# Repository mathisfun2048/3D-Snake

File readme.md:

# 3-D Snake... but polished

## Description and Exigence

The basic framework of this project came from the undercity hackathon, where me and my teammates were able to scrapyard a prototype to work. This project is the same project but refined, adding a PCB to better manage wires and audio to better communicate to the user when the snake dies. Some minor software improvements have also been made (such as re-working the moving mechanism when the snake reaches the top pannel). 

Here's a pic of our prototype:

## Schematic and PCB

During prototyping, one of the hardest parts of the design was making sure all the gpio pins stayed in place! So, I made a pcb to help with wiring. 

Here's the full wirings with the raspberry pi:

## Firmware

This project is coded in circuitpython to run on a raspberry pi pico. Most of the firmware was written at the hackathon, including the snake's game engine and wrapping mechanisms. With my improvements, a audio mechanism was added, playing a sound when the game is played and a death "game over" sound. Additionally, the joystick movements was revised, however, its effacaciy will only be able to be tested once I build it and get to callibrate the joystick.

## CAD

Here it is! It's pretty bare-bones because I want access to all the gpio and other pins for debugging. 

Here's what the game will look like with the prototype cad we made at undercity! 

## BOM
|item                |quantitiy|tot. cost|FIELD4                                                                                                                                                                                                                                                                                                                                                                                                                                                                                                                                                                                     |
|--------------------|---------|---------|-------------------------------------------------------------------------------------------------------------------------------------------------------------------------------------------------------------------------------------------------------------------------------------------------------------------------------------------------------------------------------------------------------------------------------------------------------------------------------------------------------------------------------------------------------------------------------------------|
|Raspberry Pi Pico   |1        |3.94     |https://www.aliexpress.us/item/3256805901509044.html?spm=a2g0o.productlist.main.4.dbd8ce49Pw7vDJ&aem_p4p_detail=202507160215394922763879841710000065438&algo_pvid=166d0d05-e104-4c77-8e09-4d1850dd867c&algo_exp_id=166d0d05-e104-4c77-8e09-4d1850dd867c-3&pdp_ext_f={"order":"588","eval":"1"}&pdp_npi=4@dis!USD!3.94!0.99!!!28.12!7.05!@2103245417526573392084861e1d15!12000044713099471!sea!US!6423725769!ABX&curPageLogUid=9vH35S108aDJ&utparam-url=scene:search&#124;query_from:&search_p4p_id=202507160215394922763879841710000065438_1                                                    |
|8x8 Neopixel Matrix |5        |0.99     |https://www.aliexpress.us/item/3256806907950230.html?spm=a2g0o.productlist.main.1.2bbc5ce5pLgTVv&aem_p4p_detail=202507151754542105286846737200000740401&algo_pvid=230e7d87-c7e6-4e0c-8734-1b0156b671e8&algo_exp_id=230e7d87-c7e6-4e0c-8734-1b0156b671e8-0&pdp_ext_f=%7B%22order%22%3A%2225%22%2C%22eval%22%3A%221%22%7D&pdp_npi=4%40dis%21USD%212.42%210.99%21%21%2117.26%217.08%21%402103209b17526272944055213e0d20%2112000039383600775%21sea%21US%210%21ABX&curPageLogUid=1N7nF0o4iUD7&utparam-url=scene%3Asearch%7Cquery_from%3A&search_p4p_id=202507151754542105286846737200000740401_1|
|Jumper Wire Kit     |1        |2.94     |https://www.aliexpress.us/item/3256801814340687.html?spm=a2g0o.cart.0.0.18e038daN3o7c6&mp=1&pdp_npi=5@dis!USD!USD 3.11!USD 2.94!!USD 2.94!!!@2103244817526478142373005ef927!12000018371624182!ct!US!6423725769!!1!0&_gl=1*1n0i64z*_gcl_au*MTk0MzAyNDY5MC4xNzUyNjI3MjM2*_ga*MTc1NDE4NzMwOC4xNzUyNjI3MjM3*_ga_VED1YSGNC7*czE3NTI2NDcxMjIkbzMkZzEkdDE3NTI2NDc4MzAkajE2JGwwJGgw&gatewayAdapt=glo2usa                                                                                                                                                                                           |
|7 Segment Display   |2        |0.88     |https://www.aliexpress.us/item/3256806851785862.html?spm=a2g0o.productlist.main.2.76ae5146QPECX9&algo_pvid=e750615b-f244-471b-bc4a-14b7c0dba0d7&algo_exp_id=e750615b-f244-471b-bc4a-14b7c0dba0d7-1&pdp_ext_f=%7B%22order%22%3A%221740%22%2C%22eval%22%3A%221%22%2C%22orig_sl_item_id%22%3A%221005007038100614%22%2C%22orig_item_id%22%3A%221005008653444674%22%7D&pdp_npi=4%40dis%21USD%211.97%210.89%21%21%2114.02%216.31%21%402101c80217526280440434429ebc72%2112000039179020865%21sea%21US%210%21ABX&curPageLogUid=seevTTpQwIjR&utparam-url=scene%3Asearch%7Cquery_from%3A              |
|Joystick            |1        |5.54     |https://www.aliexpress.us/item/3256807375670744.html?spm=a2g0o.productlist.0.0.4dcf732baWaYuF&mp=1&pdp_npi=5%40dis%21USD%21USD%205.55%21USD%200.99%21%21USD%200.99%21%21%21%402103246617526296646986725ef22f%2112000041302774772%21ct%21US%21-1%21%211%210&_gl=1*1cuejm7*_gcl_au*Nzg2NzU0ODQ1LjE3NTI2MjcyOTg.*_ga*MTI2NzgwMDk2Ny4xNzUyNjI3NzUy*_ga_VED1YSGNC7*czE3NTI2Mjc3NTIkbzEkZzEkdDE3NTI2Mjk2NjQkajYkbDAkaDA.&gatewayAdapt=glo2usa                                                                                                                                                    |
|Stepper Motor       |1        |6.05     |https://www.aliexpress.us/item/3256802068491329.html?spm=a2g0o.productlist.main.2.5c6722b96U4iYb&algo_pvid=ff7cea5a-0fa2-4fb9-84df-aa9c87232c42&algo_exp_id=ff7cea5a-0fa2-4fb9-84df-aa9c87232c42-1&pdp_ext_f=%7B%22order%22%3A%2294%22%2C%22eval%22%3A%221%22%7D&pdp_npi=4%40dis%21USD%2117.73%210.99%21%21%2117.73%210.99%21%402101c59517526291617727360eec60%2112000030753573944%21sea%21US%210%21ABX&curPageLogUid=7Ex5kMtxOTSK&utparam-url=scene%3Asearch%7Cquery_from%3A         https://www.amazon.com/gp/product/B00PNEQKC0/ref=ewc_pr_img_3?smid=AWQBCGWISS7BL&psc=1               |
|Stepper Motor Driver|1        |2.25     |https://www.aliexpress.us/item/3256809082535036.html?spm=a2g0o.cart.0.0.4f6638da3vPkLG&mp=1&pdp_npi=5@dis!USD!USD 4.50!USD 2.25!!USD 2.25!!!@2101ead817526549979955339eefa0!12000048551339904!ct!US!6423725769!!1!0&_gl=1*1jo1tpj*_gcl_au*MTk0MzAyNDY5MC4xNzUyNjI3MjM2*_ga*MTc1NDE4NzMwOC4xNzUyNjI3MjM3*_ga_VED1YSGNC7*czE3NTI2NTMwNjIkbzQkZzEkdDE3NTI2NTQ5OTgkajU5JGwwJGgw&gatewayAdapt=glo2usa                                                                                                                                                                                           |
|9v Battery          |2        |0        |n/a                                                                                                                                                                                                                                                                                                                                                                                                                                                                                                                                                                                        |
|9V Battery Wire     |2        |1.35     |https://www.aliexpress.us/item/3256806021864359.html?spm=a2g0o.productlist.main.1.3cdc63faZErZgJ&algo_pvid=79f0a5c4-7072-47e4-94d5-bd7585c02c02&algo_exp_id=79f0a5c4-7072-47e4-94d5-bd7585c02c02-0&pdp_ext_f=%7B%22order%22%3A%22872%22%2C%22eval%22%3A%221%22%7D&pdp_npi=4%40dis%21USD%211.39%210.99%21%21%219.90%217.01%21%402103244817526291003078319ef997%2112000036283911965%21sea%21US%210%21ABX&curPageLogUid=NyxoG5DCxoBX&utparam-url=scene%3Asearch%7Cquery_from%3A                                                                                                               |
|I2C Audio Module    |1        |2.13     |https://www.aliexpress.us/item/3256807442706139.html?spm=a2g0o.cart.0.0.337d38daaIdRcX&mp=1&pdp_npi=5@dis!USD!USD 2.18!USD 2.13!!USD 2.13!!!@2103146c17526564969422213ebb51!12000041565703118!ct!US!6423725769!!1!0&_gl=1*zdge7z*_gcl_au*MTk0MzAyNDY5MC4xNzUyNjI3MjM2*_ga*MTc1NDE4NzMwOC4xNzUyNjI3MjM3*_ga_VED1YSGNC7*czE3NTI2NTMwNjIkbzQkZzEkdDE3NTI2NTY0ODMkajU4JGwwJGgw&gatewayAdapt=glo2usa                                                                                                                                                                                            |
|Speaker             |1        |1.84     |https://www.aliexpress.us/item/3256805513567413.html?spm=a2g0o.productlist.main.2.62921545em6tZ4&algo_pvid=6fd662af-376f-43c8-b7bc-04e676755f85&algo_exp_id=6fd662af-376f-43c8-b7bc-04e676755f85-1&pdp_ext_f={"order":"521","eval":"1"}&pdp_npi=4@dis!USD!1.91!0.99!!!13.62!7.02!@2103247417526569339281477efc58!12000044410928207!sea!US!6423725769!ABX&curPageLogUid=dsVUW3rp1g8F&utparam-url=scene:search&#124;query_from:                                                                                                                                                                   |
|header pins         |1        |2.21     |https://www.aliexpress.us/item/2255800687544049.html?spm=a2g0o.productlist.main.3.33dd552fLOHpHk&algo_pvid=4a50cbd5-7957-4d16-a3ac-91a9c1a7af24&algo_exp_id=4a50cbd5-7957-4d16-a3ac-91a9c1a7af24-2&pdp_ext_f={"order":"3500","eval":"1"}&pdp_npi=4@dis!USD!2.21!0.99!!!2.21!0.99!@2101e07217526574650792034e0f2b!10000010058190554!sea!US!6423725769!ABX&curPageLogUid=oeRbzI77IVV5&utparam-url=scene:search&#124;query_from:                                                                                                                                                                   |
|pcb                 |1        |6.22     |https://jlcpcb.com/                                                                                                                                                                                                                                                                                                                                                                                                                                                                                                                                                                        |
|                    |         |36.34    |                                                                                                                                                                                                                                                                                                                                                                                                                                                                                                                                                                                           |

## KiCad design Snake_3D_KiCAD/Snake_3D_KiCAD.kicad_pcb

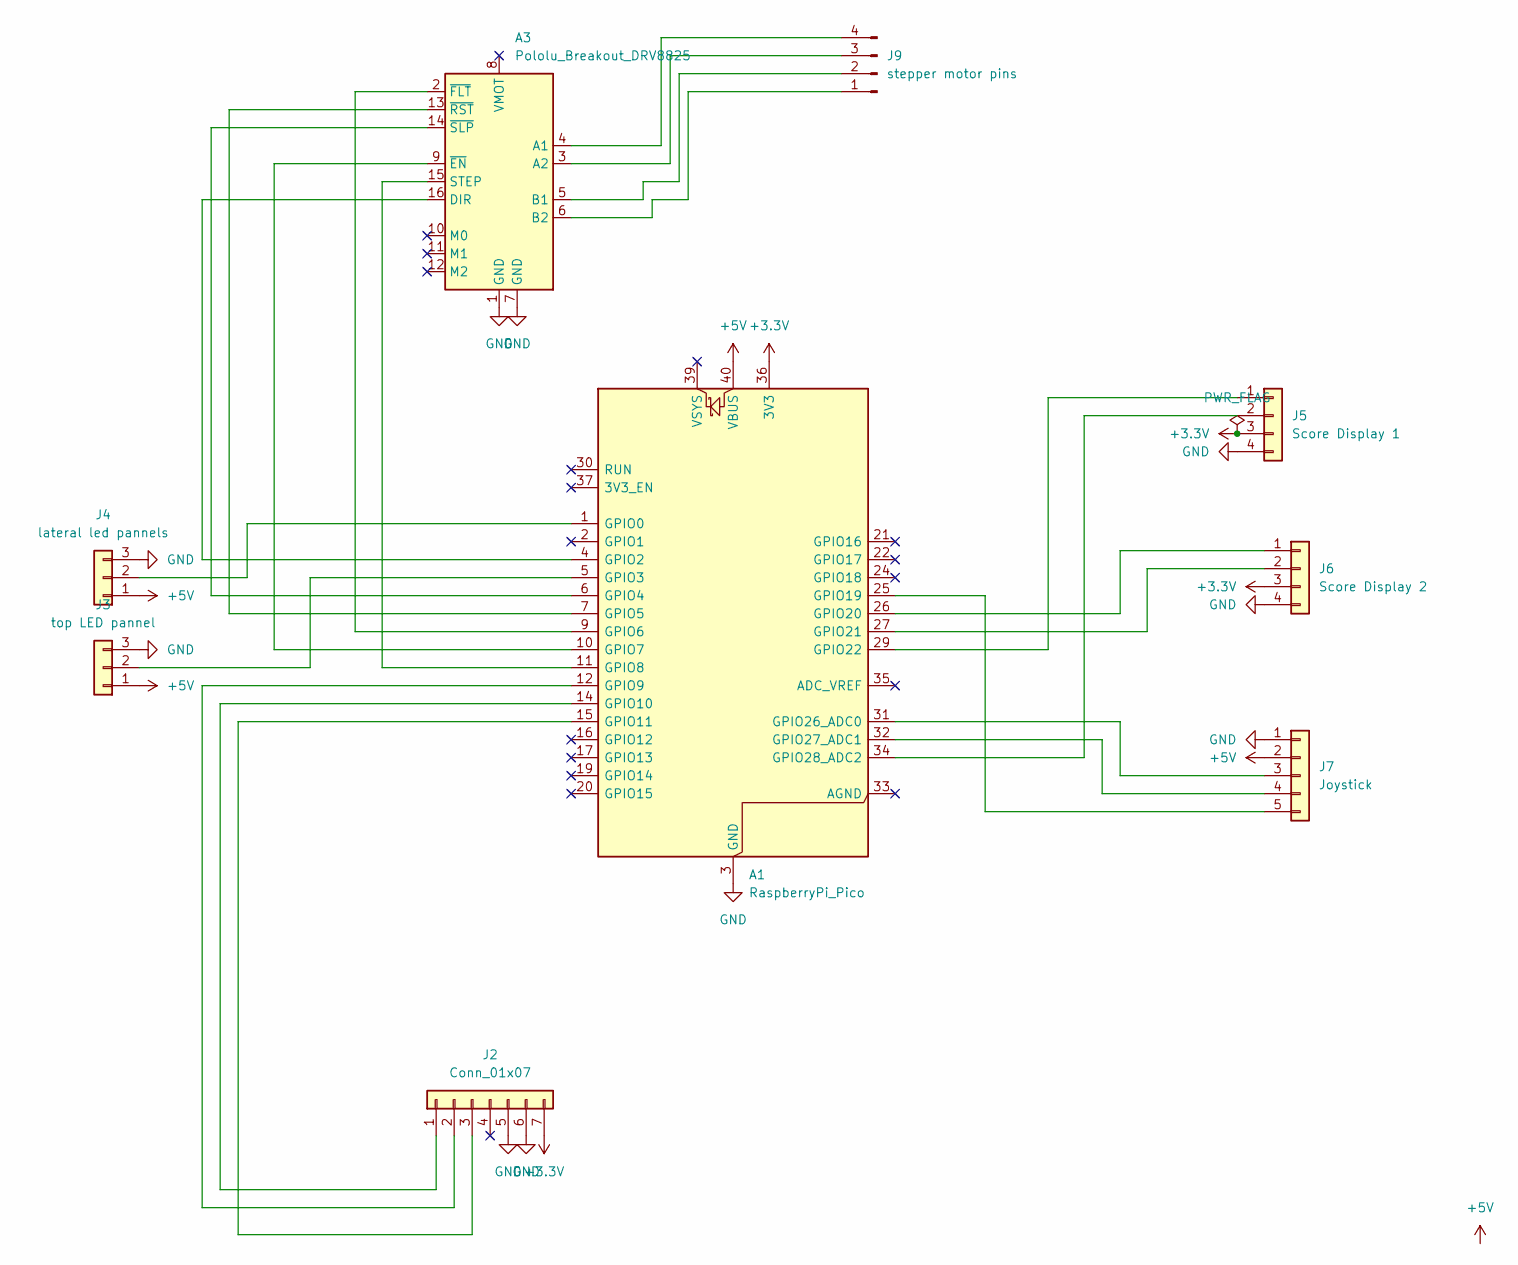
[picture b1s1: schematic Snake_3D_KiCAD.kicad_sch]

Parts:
A1: RaspberryPi_Pico; RaspberryPi_Pico_Common_Unspecified
A3: Pololu_Breakout_DRV8825; Pololu_Breakout-16_15.2x20.3mm
J2: Conn_01x07; PinHeader_1x07_P2.54mm_Vertical
J3: top LED pannel; PinHeader_1x03_P2.54mm_Vertical
J4: lateral led pannels; PinHeader_1x03_P2.54mm_Vertical
J5: Score Display 1; PinHeader_1x04_P2.54mm_Vertical
J6: Score Display 2; PinHeader_1x04_P2.54mm_Vertical
J7: Joystick; PinHeader_1x05_P2.54mm_Vertical
J9: stepper motor pins; PinHeader_1x04_P2.54mm_Vertical

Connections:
+3.3V: A1.36 (3V3), J2.7, J5.3 (VCC), J6.3 (VCC)
+5V: A1.40 (VBUS), J3.1 (VIN), J4.1 (VIN), J7.2 (+5V)
GND: A1.3 (GND), A1.8 (GND), A1.13 (GND), A1.18 (GND), A1.23 (GND), A1.28 (GND), A1.38 (GND), A3.1 (GND), A3.7 (GND), J2.5, J2.6, J3.3 (GND), J4.3 (GND), J5.4 (GND), J6.4 (GND), J7.1 (GND)
unnamed: A1.1 (GPIO0), J4.2 (DIN_0)
unnamed: A1.4 (GPIO2), A3.16 (DIR)
unnamed: A1.5 (GPIO3), J3.2 (DIN_0)
unnamed: A1.6 (GPIO4), A3.14 (~SLP)
unnamed: A1.7 (GPIO5), A3.13 (~RST)
unnamed: A1.9 (GPIO6), A3.2 (~FLT)
unnamed: A1.10 (GPIO7), A3.9 (~EN)
unnamed: A1.11 (GPIO8), A3.15 (STEP)
unnamed: A1.12 (GPIO9), J2.2
unnamed: A1.14 (GPIO10), J2.1
unnamed: A1.15 (GPIO11), J2.3
unnamed: A1.25 (GPIO19), J7.5 (SW)
unnamed: A1.26 (GPIO20), J6.1 (CLK)
unnamed: A1.27 (GPIO21), J6.2 (DIO)
unnamed: A1.29 (GPIO22), J5.1 (CLK)
unnamed: A1.31 (GPIO26_ADC0), J7.3 (VRX)
unnamed: A1.32 (GPIO27_ADC1), J7.4 (VRY)
unnamed: A1.34 (GPIO28_ADC2), J5.2 (DIO)
unnamed: A3.4 (A1), J9.4 (A1)
unnamed: A3.3 (A2), J9.3 (A2)
unnamed: A3.5 (B1), J9.2 (B1)
unnamed: A3.6 (B2), J9.1 (B2)

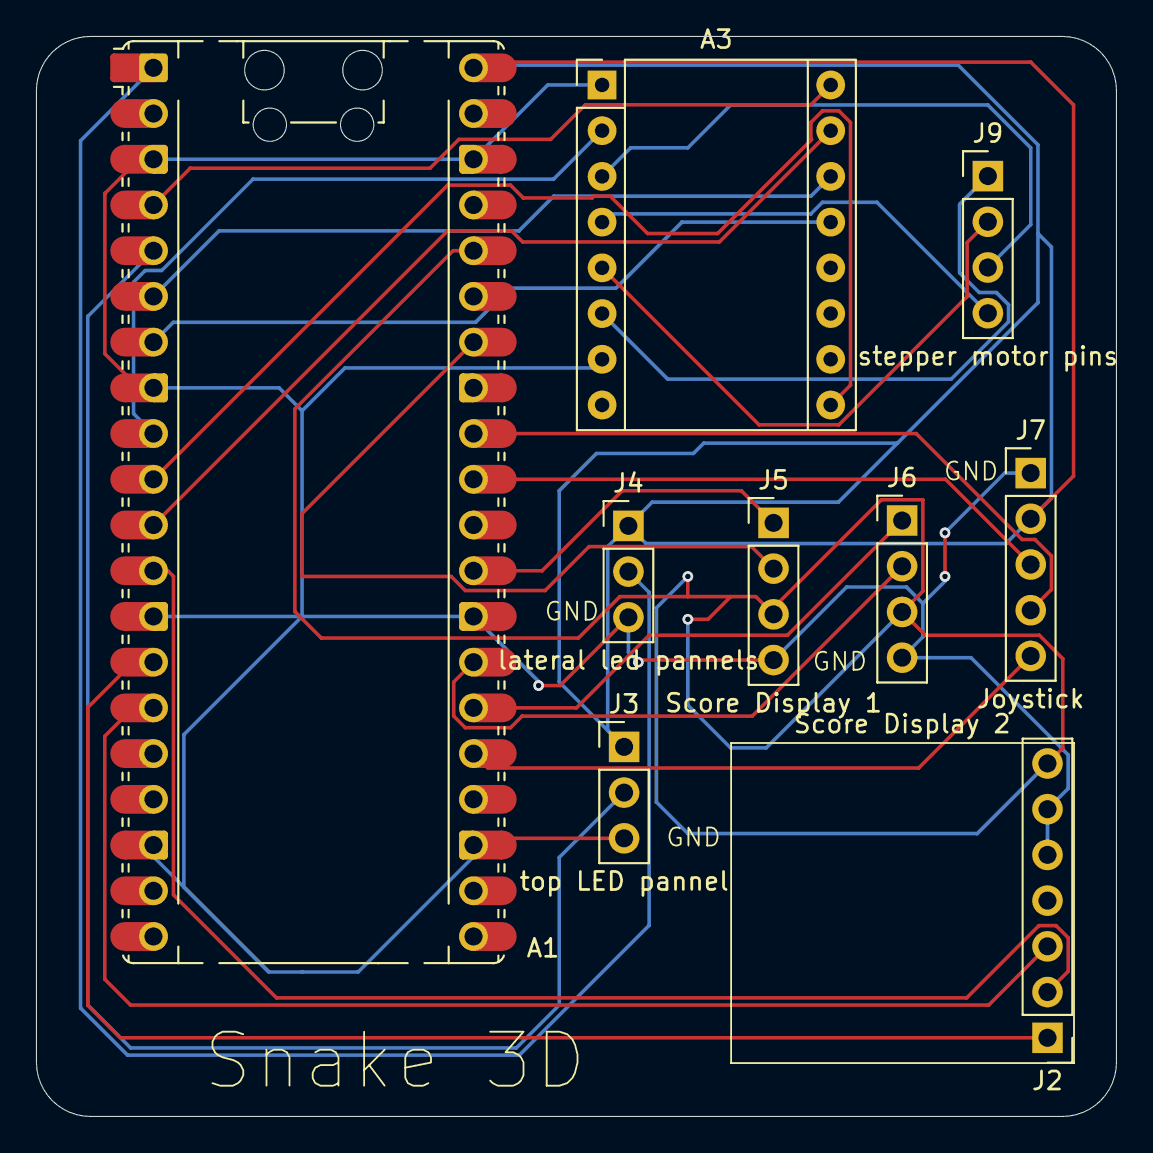
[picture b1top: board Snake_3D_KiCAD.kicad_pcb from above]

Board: 2 copper layers, 60.0 x 60.0 mm, 9 parts (0 on the bottom side), 25 nets.

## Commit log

2025-07-16 created readme.md
2025-07-16 set up file structure
2025-07-16 continued working on pcb
2025-07-16 finished pcb design
2025-07-16 added gerber files
2025-07-16 finished designing 3d case
2025-07-16 pcb updates
2025-07-16 worked on formatting everything for submission
